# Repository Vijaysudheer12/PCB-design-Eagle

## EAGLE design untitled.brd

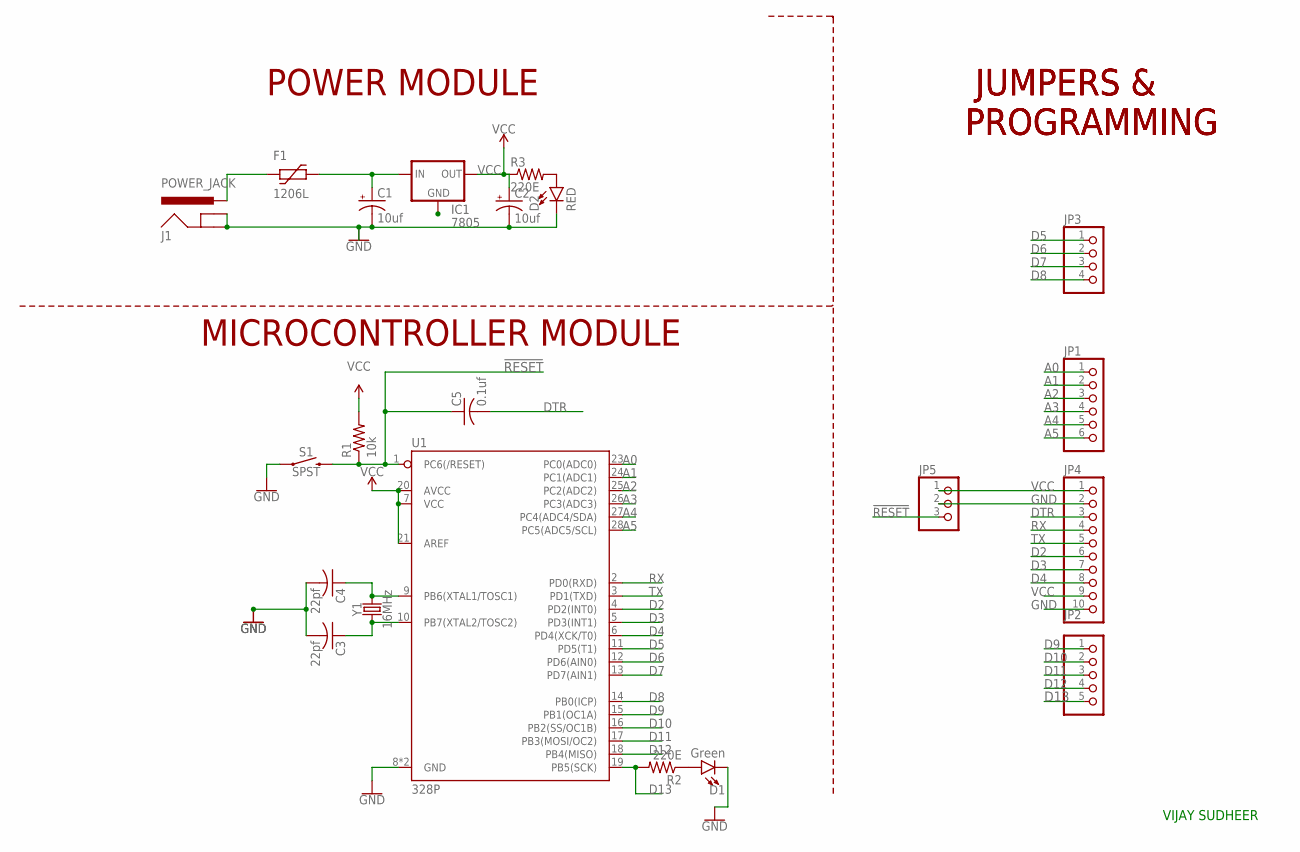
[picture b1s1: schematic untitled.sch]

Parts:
C1, C2: 10uf; E2,5-6E
C3, C4: 22pf; C025-024X044
C5: 0.1uf; C025-024X044
D1: Green; LED_5MM
D2: RED; LED_5MM
F1: 1206L
IC1: 7805; 78XXS
J1: POWER_JACK; POWER_JACK_PTH
JP1: PINHD-1X6; 1X06
JP2: PINHD-1X5; 1X05
JP3: PINHD-1X4; 1X04
JP4: PINHD-1X10; 1X10
JP5: PINHD-1X3; 1X03
R1: 10k; 0204/7
R2, R3: 220E; 0204/7
S1: SPST; TACTILE_SWITCH_PTH_6.0MM
U1: 328P; DIP28
Y1: 16MHz; HC49US

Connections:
!RESET: C5.1, JP5.3, R1.1, S1.3 (2), U1.1 (PC6(/RESET))
A0: JP1.1, U1.23 (PC0(ADC0))
A1: JP1.2, U1.24 (PC1(ADC1))
A2: JP1.3, U1.25 (PC2(ADC2))
A3: JP1.4, U1.26 (PC3(ADC3))
A4: JP1.5, U1.27 (PC4(ADC4/SDA))
A5: JP1.6, U1.28 (PC5(ADC5/SCL))
D2: JP4.6, U1.4 (PD2(INT0))
D3: JP4.7, U1.5 (PD3(INT1))
D4: JP4.8, U1.6 (PD4(XCK/T0))
D5: JP3.1, U1.11 (PD5(T1))
D6: JP3.2, U1.12 (PD6(AIN0))
D7: JP3.3, U1.13 (PD7(AIN1))
D8: JP3.4, U1.14 (PB0(ICP))
D9: JP2.1, U1.15 (PB1(OC1A))
D10: JP2.2, U1.16 (PB2(SS/OC1B))
D11: JP2.3, U1.17 (PB3(MOSI/OC2))
D12: JP2.4, U1.18 (PB4(MISO))
D13: JP2.5, R2.2, U1.19 (PB5(SCK))
DTR: C5.2, JP4.3
GND: C1.-, C2.-, C3.2, C4.2, D1.K (C), D2.K (C), J1.GND, J1.GNDBREAK, JP4.2, JP4.10, JP5.2, S1.1, U1.8 (GND), U1.22 (GND)
unnamed: C4.1, U1.9 (PB6(XTAL1/TOSC1)), Y1.2
unnamed: C1.+, F1.P$2 (2), IC1.IN
unnamed: C3.1, U1.10 (PB7(XTAL2/TOSC2)), Y1.1
unnamed: D2.A, R3.2
unnamed: F1.P$1 (1), J1.PWR
unnamed: D1.A, R2.1
RX: JP4.4, U1.2 (PD0(RXD))
TX: JP4.5, U1.3 (PD1(TXD))
VCC: C2.+, IC1.OUT, JP4.1, JP4.9, JP5.1, R1.2, R3.1, U1.7 (VCC), U1.20 (AVCC), U1.21 (AREF)

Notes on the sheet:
POWER MODULE
MICROCONTROLLER MODULE
JUMPERS & PROGRAMMING
VIJAY SUDHEER

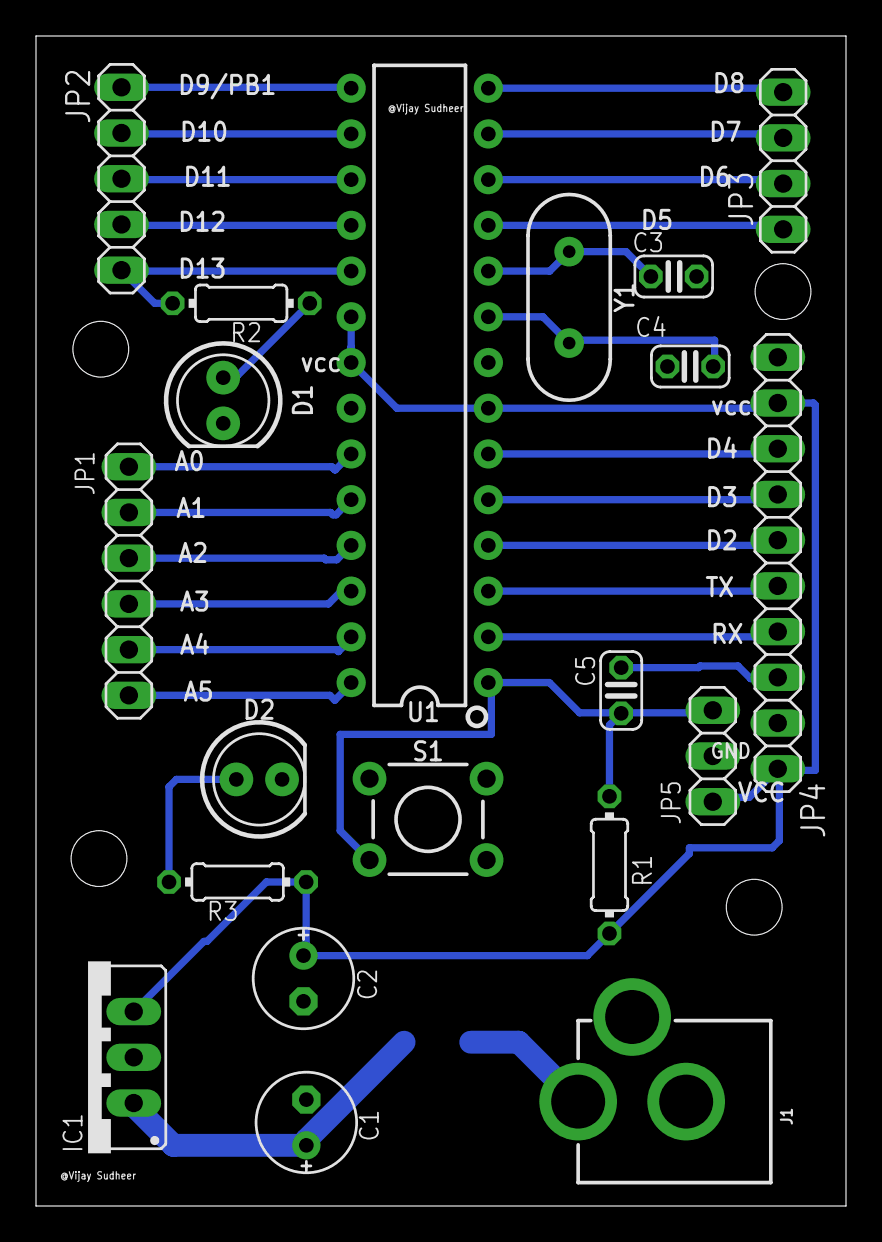
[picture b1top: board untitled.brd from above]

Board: 2 copper layers, 45.0 x 65.0 mm, 21 parts (1 on the bottom side), 30 nets.

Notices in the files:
parts and their libraries:
SparkFun-LED: Licensing: Creative Commons ShareAlike 4.0 International - https://creativecommons.org/licenses/by-sa/4.0
